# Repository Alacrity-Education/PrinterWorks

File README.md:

# PrinterWorks

Our 3D printer mods and PCB's

| [CANDU](CANDU) | [INDXWorx](INDXWorx) | [KliFan](KliFan) |
| :--: | :--: | :--: |
|  |  |  |

| [PIPSU](PIPSU) | [PDU20V](PDU20V) |
| :--: | :--: |
|  |  |

## RBARF

| [V0.1](RBARF-V0.1) | [V0.2](RBARF-V0.2) | [V0.3](RBARF-V0.3) |
| :--: | :--: | :--: |
|  |  |  |

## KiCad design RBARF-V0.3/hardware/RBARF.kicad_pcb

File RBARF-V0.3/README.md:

# RBARF V0.3

The same board as [RBARF V0.2](../RBARF-V0.2) (STM32C011D6, TPS7A02 LDO), with
the Q1 MOSFET footprint fixed.

Programming and debug pads: `SWDIO`, `SWCLK` and `UART`.

|  |  |
| -- | -- |

## Firmware

Rust + Embassy, in `firmware/`. See [firmware/README.md](firmware/README.md).

```sh
cd firmware
cargo build --release
cargo run --release    # flash with probe-rs
```

The C parity test (`cargo test-anim`) compiles the V0.1 animation engine from
`RBARF-V0.1/firmware/app/`.

The same firmware runs on [V0.2](../RBARF-V0.2).

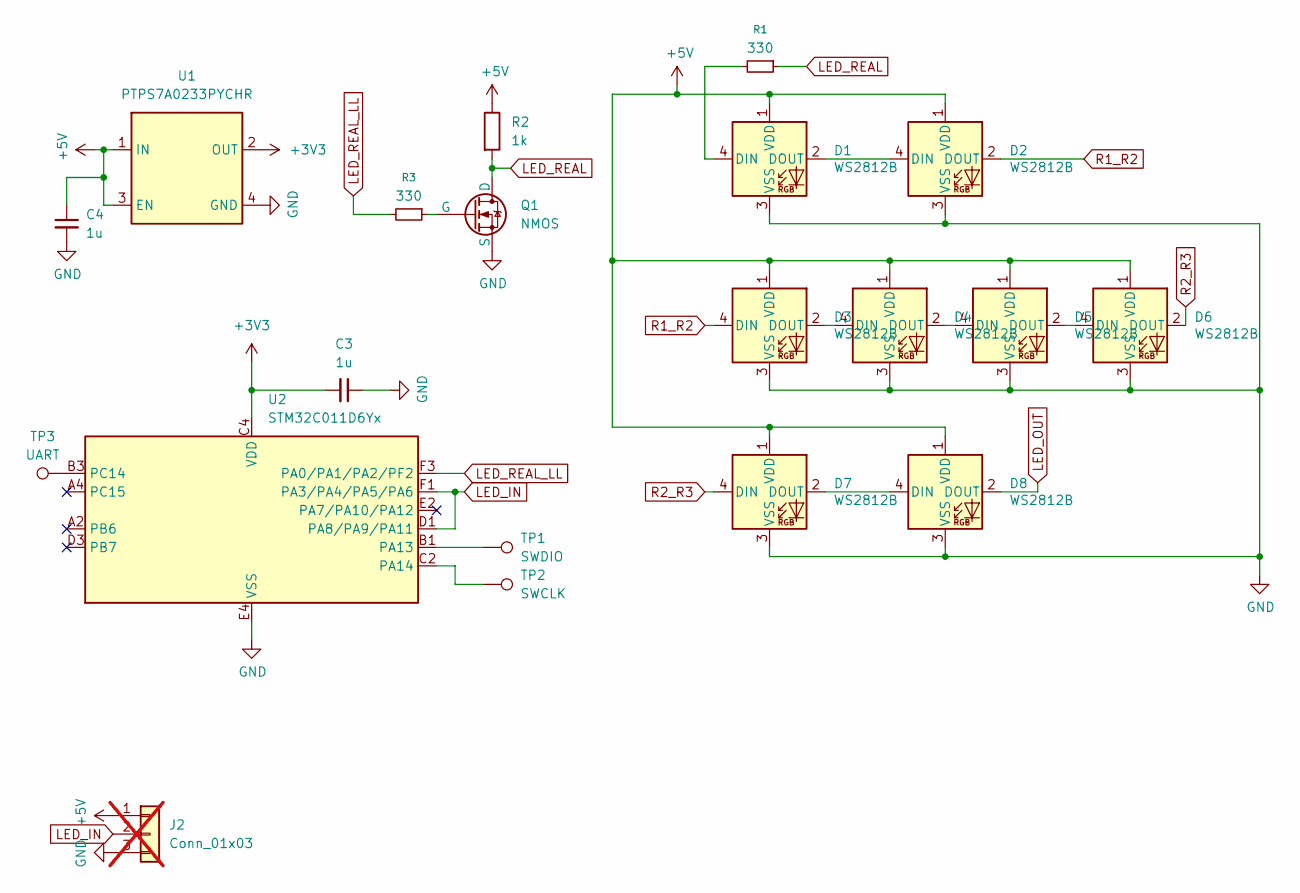
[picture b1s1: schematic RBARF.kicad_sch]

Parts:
C3, C4: 1u; C_0603_1608Metric; LCSC C29936
D1, D2, D3, D4, D5, D6, D7, D8: WS2812B; WS2812B-2020
J2: Conn_01x03; PinHeader_1x03_P1.00mm_Vertical_SMD_Pin1Left; not fitted
Q1: NMOS; TRXDFN100X60X40-3N
R1, R3: 330; R_0402_1005Metric; LCSC C105875
R2: 1k; R_0402_1005Metric
TP1: SWDIO; TestPoint_Pad_D1.0mm
TP2: SWCLK; TestPoint_Pad_D1.0mm
TP3: UART; TestPoint_Pad_D1.0mm
U1: PTPS7A0233PYCHR; YCH0004A-MFG
U2: STM32C011D6Yx; ST_WLCSP-12_1.7x1.42mm_Layout4x6_P0.35mm_Stagger

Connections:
+3V3: C3.2, U1.2 (OUT), U2.C4 (VDD)
+5V: C4.1, D1.1 (VDD), D2.1 (VDD), D3.1 (VDD), D4.1 (VDD), D5.1 (VDD), D6.1 (VDD), D7.1 (VDD), D8.1 (VDD), J2.1, R2.1, U1.1 (IN), U1.3 (EN)
GND: C3.1, C4.2, D1.3 (VSS), D2.3 (VSS), D3.3 (VSS), D4.3 (VSS), D5.3 (VSS), D6.3 (VSS), D7.3 (VSS), D8.3 (VSS), J2.3, Q1.3 (S), U1.4 (GND), U2.E4 (VSS)
LED_IN: J2.2, U2.D1 (PA8/PA9/PA11), U2.F1 (PA3/PA4/PA5/PA6)
LED_OUT: D8.2 (DOUT)
LED_REAL: Q1.1 (D), R1.1, R2.2
LED_REAL_LL: R3.2, U2.F3 (PA0/PA1/PA2/PF2)
unnamed: D1.4 (DIN), R1.2
unnamed: D1.2 (DOUT), D2.4 (DIN)
unnamed: D3.2 (DOUT), D4.4 (DIN)
unnamed: D4.2 (DOUT), D5.4 (DIN)
unnamed: D5.2 (DOUT), D6.4 (DIN)
unnamed: D7.2 (DOUT), D8.4 (DIN)
unnamed: Q1.2 (G), R3.1
unnamed: TP1.1 (1_1), U2.B1 (PA13)
unnamed: TP2.1 (1_1), U2.C2 (PA14)
unnamed: TP3.1 (1_1), U2.B3 (PC14)
R1_R2: D2.2 (DOUT), D3.4 (DIN)
R2_R3: D6.2 (DOUT), D7.4 (DIN)

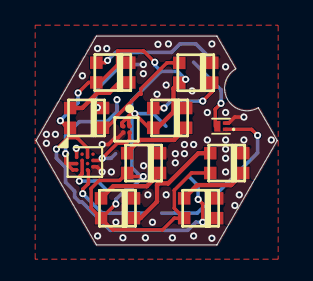
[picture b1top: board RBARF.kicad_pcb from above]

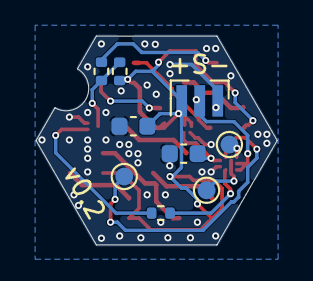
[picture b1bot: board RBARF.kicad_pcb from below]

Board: 2 copper layers, 13.4 x 11.6 mm, 20 parts (9 on the bottom side), 18 nets.

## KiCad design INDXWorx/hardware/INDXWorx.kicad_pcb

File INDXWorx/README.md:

# INDXWorx V0.1

An adapter that connects the Bondtech INDX Prusa head to a Klipper printer. It
is designed to plug into the BTT Octopus mainboard.

The head talks RS485. The board carries an ST STR485, a very high quality
RS485 transceiver, and gives the head switchable 5V power.

|  |  |
| -- | -- |

## Features

- **RS485** through the ST STR485 transceiver, with 120 Ω termination on the
  board.
- **Very good ESD protection and common-mode rejection** on the RS485 line: a
  common-mode choke (Murata DLW43SH), an ESD protection diode (NUP2105L) and
  100 pF C0G filter capacitors.
- **Clean supplies:** a TI TPS60151 flying-capacitor charge pump makes a clean
  5V from the Octopus 3.3V, and an MCP1825 LDO makes the board's own 3.3V.
- **Switchable 5V head power**, through a P-MOSFET.
- **LEDs** for board power, 5V head power and RS485 activity.
- **RS485 line swapper:** a DIP switch poka-yoke, so the two RS485 lines can be
  swapped without re-crimping the cable.

## Connections

### Octopus

The board plugs into the Octopus WiFi socket. It uses these Octopus pins:

| Octopus pin | Function |
| -- | -- |
| PD5 (TX3) | RS485 transmit |
| PD6 (RX3) | RS485 receive |
| PD7 | RS485 driver enable (DE) |
| PD10 | RS485 receiver enable (/RE, active low) |
| PG7 | Head 5V switch: on by default, drive high to switch the head off |

### Head

## RS485 line swapper

The silkscreen next to the DIP switch shows the two settings:

- **Straight (`| |`):** the two switches next to `| |` ON, the two next to
  `X` OFF.
- **Swapped (`X`):** the two switches next to `X` ON, the two next to `| |`
  OFF. The head's two RS485 lines are crossed.

Go by the silkscreen marks, not the numbers on the switch: the switch can be
fitted either way round.

Use one pair at a time: turning on all four switches shorts the RS485 lines.

## LEDs

The silkscreen `T/H/P` names the three LEDs:

- **T** (blue): traffic, RS485 activity.
- **H** (red): head power, the switched 5V to the head is on.
- **P** (orange): board power.

## Options

- `JP4` (`SLR`, on the back) is a solder jumper, open by default. Closing it
  ties the STR485 slew-rate pin to 3.3V; see the STR485 datasheet.

## Gallery

|  |  |
| -- | -- |
|  |  |
|  |  |

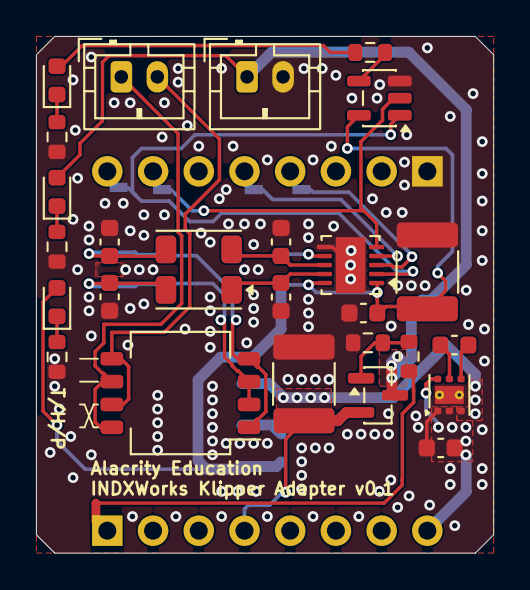
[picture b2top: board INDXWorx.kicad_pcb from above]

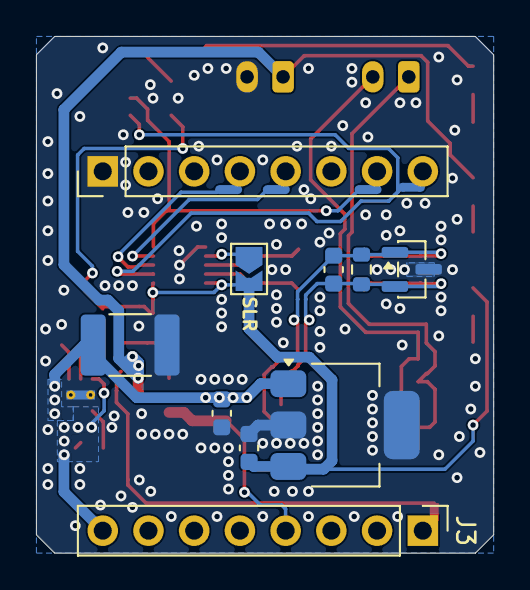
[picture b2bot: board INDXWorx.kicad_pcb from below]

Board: 2 copper layers, 25.4 x 28.7 mm, 41 parts (14 on the bottom side), 30 nets.

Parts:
C7, C8, C9, C10, C11: 100p; C_0603_1608Metric
C13, C14, C19: 10u; C_1812_4532Metric
C15: 100n; C_0603_1608Metric
C16, C17: 1u; C_0603_1608Metric
C18: 2.2u; C_0603_1608Metric
C20: 10u; C_0603_1608Metric
D2: NUP2105L; SOT-23
D3: PWR-ORANGE; LED_0603_1608Metric
D4: HEAD-RED; LED_0603_1608Metric
D5: PWR-BLUE; LED_0603_1608Metric
J3: WIFISOCKET_P1; PinHeader_1x08_P2.54mm_Vertical
J4: WIFISOCKET_P2; PinHeader_1x08_P2.54mm_Vertical
J8: RS485; JST_PH_B2B-PH-K_1x02_P2.00mm_Vertical
J9: 5V_SW; JST_PH_B2B-PH-K_1x02_P2.00mm_Vertical
JP4: SLR; SolderJumper-2_P1.3mm_Open_TrianglePad1.0x1.5mm
L2: muRata DLW43SH510XK2L; L_CommonModeChoke_Coilank_ACM4532
NT1, NT2, NT3, NT4, NT5: NetTie_2; NetTie-2_SMD_Pad0.5mm
Q1: AO3401A; SOT-23
R6, R8, R11, R12: 120; R_0603_1608Metric
R7: 10K; R_0603_1608Metric
R9, R10: 470; R_0603_1608Metric
SW3: LINE_SWAPPER; SW_DIP_SPSTx04_Slide_KingTek_DSHP04TS_W7.62mm_P1.27mm
U3: STR485; DFN-10-1EP_3x3mm_P0.5mm_EP1.646x3.1mm
U4: MCP1825S-3302E; SOT-223-3_TabPin2
U5: TPS60151DRV; WSON-6-1EP_2x2mm_P0.65mm_EP1x1.6mm_ThermalVias
U7: 74AHC1G02; SOT-23-5

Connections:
3V3_RAW: C20.1, J3.8, U5.2 (VIN), U5.6 (ENA)
5V_SW_GPIO: NT1.1, R8.1
+3.3V: C14.1, C15.1, C16.1, D3.2 (A), JP4.2 (B), U3.1 (VL), U3.10 (VCC), U4.3 (VO), U7.5 (VCC)
+5V: C13.1, C17.1, C19.1, J3.4, Q1.2 (S), U4.1 (VI), U5.3 (VOUT)
/5V_SW: D4.2 (A), J9.1, Q1.3 (D)
/RS485_CHIP+: C10.1, C11.1, D2.1 (K), L2.3, R6.1, SW3.1, SW3.4
/RS485_CHIP-: C9.1, C11.2, D2.2 (K), L2.2, R6.2, SW3.2, SW3.3
/RS485_HEAD+: J8.1, SW3.6, SW3.8
/RS485_HEAD-: J8.2, SW3.5, SW3.7
GND: C7.2, C8.2, C9.2, C10.2, C13.2, C14.2, C15.2, C16.2, C17.2, C19.2, C20.2, D2.3 (A), J4.1, J9.2, R7.1, R9.2, R10.2, R11.2, U3.6 (GND), U3.11 (GND), U4.2 (GND), U5.1 (GND), U5.7 (EP), U7.3 (GND)
MB_PD5/TX3: J4.7, NT5.2
MB_PD6/RX3: J4.8, NT2.2
MB_PD7: J4.4, NT4.2
MB_PD10: J4.5, NT3.2
MB_PG7: J3.1, NT1.2
unnamed: D3.1 (K), R10.1
unnamed: D4.1 (K), R9.1
unnamed: D5.2 (A), R12.1
unnamed: D5.1 (K), R11.1
unnamed: JP4.1 (A), U3.7 (SLR)
unnamed: Q1.1 (G), R7.2, R8.2
unnamed: R12.2, U7.4
unnamed: C7.1, L2.4, U3.8 (A)
unnamed: C8.1, L2.1, U3.9 (B)
unnamed: C18.1, U5.4 (CP+)
unnamed: C18.2, U5.5 (CP-)
RS485_DE: NT4.1, U3.3 (DE)
RS485_RX: NT2.1, U3.2 (R), U7.1
RS485_TX: NT5.1, U3.5 (D), U7.2
~RS485_RE: NT3.1, U3.4 (~RE)

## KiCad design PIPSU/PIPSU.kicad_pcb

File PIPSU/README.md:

# PIPSU

A tiny PSU for Raspberry Pi boards. It plugs straight into the Pi's USB-C
port and supplies 5V, up to 3A, from the printer's 24V supply line (it accepts
8-30V). We built it to take the Raspberry Pi's power draw off the mainboard's
regulator and use a more stable supply instead.

|  |  |  |
| -- | -- | -- |

The board uses TI's TPSM63603, an ultra-integrated power module, to keep the
footprint very small. Its high efficiency keeps the temperature manageable at
full load, on a very small board with completely passive cooling.

## Connections

All the pads are on the back of the board:

- **24V** and **GND** (large pads): the input from the printer's 24V supply
  (8-30V).
- **5V** and **GND** (small pads): 5V out, for powering peripherals.
- **DP** and **DN**: the USB 2.0 data lines of the USB-C plug, for connecting
  a USB device to the Pi.

The USB-C plug advertises a 3A source to the Pi on its CC line.

|  |  |
| -- | -- |

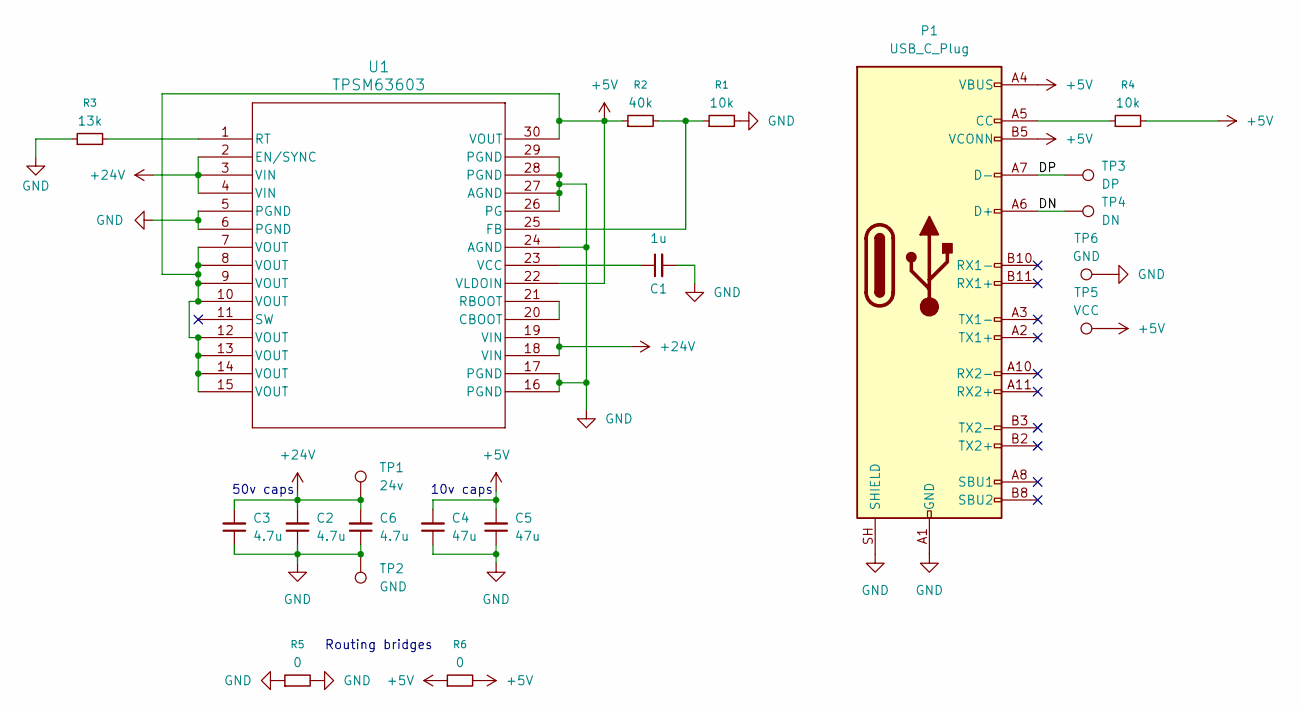
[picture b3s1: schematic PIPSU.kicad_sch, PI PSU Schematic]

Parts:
C1: 1u; C_0603_1608Metric; LCSC C29936
C2, C3, C6: 4.7u; C_1206_3216Metric; LCSC C51205
C4, C5: 47u; C_1210_3225Metric; LCSC C84494
P1: USB_C_Plug; USB_C_Plug_Molex_105444
R1, R4: 10k; R_0402_1005Metric; LCSC C2906861
R2: 40k; R_0402_1005Metric; LCSC C49654409
R3: 13k; R_0402_1005Metric; LCSC C2909319
R5, R6: 0; R_0805_2012Metric; LCSC C2907215
TP1: 24v; TestPoint_Pad_3.0x3.0mm
TP2: GND; TestPoint_Pad_3.0x3.0mm
TP3: DP; TestPoint_Pad_D1.0mm
TP4: DN; TestPoint_Pad_D1.0mm
TP5: VCC; TestPoint_Pad_D1.0mm
TP6: GND; TestPoint_Pad_D1.0mm
U1: TPSM63603; B0QFN30; LCSC C5219327

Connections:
+5V: C4.2, C5.2, P1.A4 (VBUS), P1.A9 (VBUS), P1.B4 (VBUS), P1.B5 (VCONN), P1.B9 (VBUS), R2.1, R4.2, R6.1, R6.2, TP5.1 (1_1), U1.7 (VOUT), U1.8 (VOUT), U1.9 (VOUT), U1.10 (VOUT), U1.12 (VOUT), U1.13 (VOUT), U1.14 (VOUT), U1.15 (VOUT), U1.22 (VLDOIN), U1.30 (VOUT)
+24V: C2.2, C3.2, C6.2, TP1.1 (1_1), U1.2 (EN/SYNC), U1.3 (VIN), U1.4 (VIN), U1.18 (VIN), U1.19 (VIN)
/DN: P1.A6 (D+), TP4.1 (1_1)
/DP: P1.A7 (D-), TP3.1 (1_1)
GND: C1.2, C2.1, C3.1, C4.1, C5.1, C6.1, P1.A1 (GND), P1.A12 (GND), P1.B1 (GND), P1.B12 (GND), P1.SH (SHIELD), R1.2, R3.1, R5.1, R5.2, TP2.1 (1_1), TP6.1 (1_1), U1.5 (PGND), U1.6 (PGND), U1.16 (PGND), U1.17 (PGND), U1.24 (AGND), U1.26 (PG), U1.27 (AGND), U1.28 (PGND), U1.29 (PGND)
unnamed: P1.A5 (CC), R4.1
unnamed: U1.20 (CBOOT), U1.21 (RBOOT)
unnamed: R1.1, R2.2, U1.25 (FB)
unnamed: R3.2, U1.1 (RT)
unnamed: C1.1, U1.23 (VCC)

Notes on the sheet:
Routing bridges
10v caps
50v caps

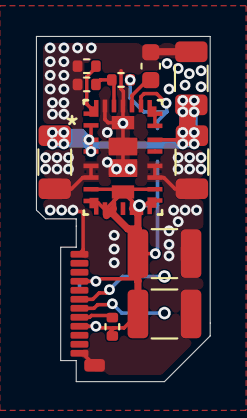
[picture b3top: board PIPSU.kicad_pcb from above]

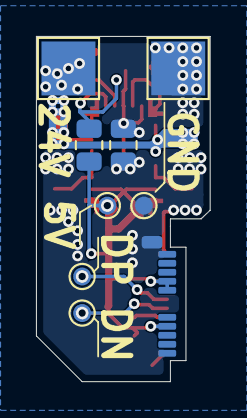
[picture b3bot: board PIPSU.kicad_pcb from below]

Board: 2 copper layers, 9.7 x 19.2 mm, 20 parts (8 on the bottom side), 10 nets.

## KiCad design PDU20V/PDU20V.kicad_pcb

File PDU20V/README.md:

# PDU20V

A rack power distribution board. It takes 20V from one big supply and shares
it out to the mini PCs and other devices in the rack, over XT90 connectors.

|  |  |
| -- | -- |

## Connectors

- **PSU side (J6, back of the board)**: one female AMASS XT90, for the lead
  from the 20V supply.
- **Outputs (J1-J5, J7-J10, front)**: nine male AMASS XT90s, one per mini PC
  or device.
- **Solder pads (TP1-TP4, back)**: two `+20V` and two `GND` 4×4mm pads, for
  wiring the supply or measuring.

All connectors are in parallel: every output gets the full 20V rail. There is
no fuse or switch on the board.

|  |
| -- |
|  |

## Mounting

The ten M3 holes are not isolated: the five along one long edge are on `+20V`
and the five along the other are on `GND`. Mount the board with nylon
standoffs or screws, or it will short the supply against a metal rack.

## Mini PCs

We use it with Dell OptiPlex 3060 Micro PCs. Fed from a shared supply instead
of the Dell charger, their BIOS throttles the CPU to 800 MHz.
[Dell3060ForcePower](https://github.com/Alacrity-Education/Dell3060ForcePower)
restores full clocks and turbo at every boot.

We use this board in our rack to save space and power: all the mini PCs run
from a single supply instead of one power brick each.

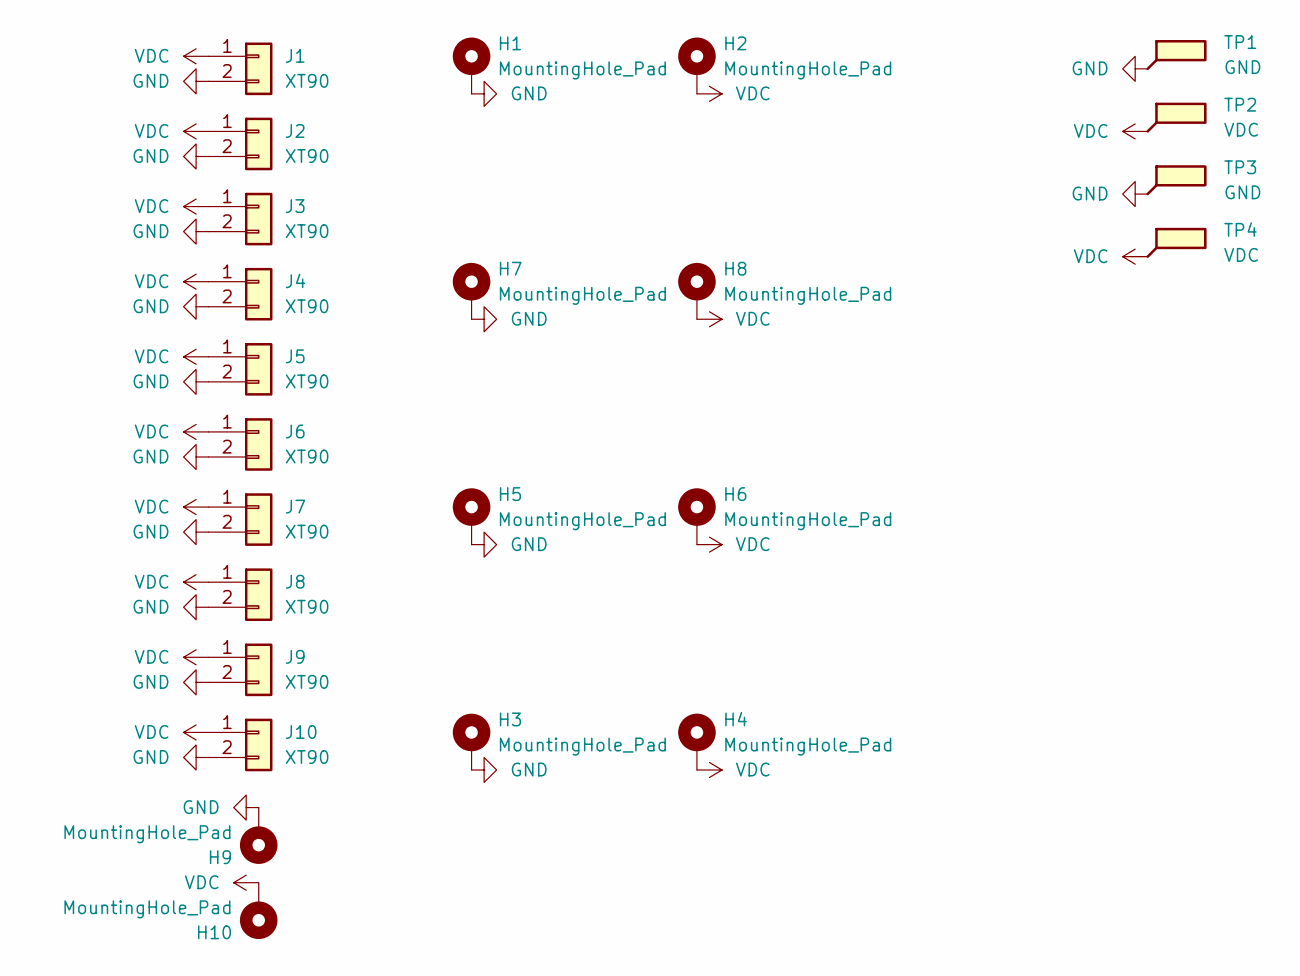
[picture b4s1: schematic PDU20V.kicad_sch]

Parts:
H1, H2, H3, H4, H5, H6, H7, H8, H9, H10: MountingHole_Pad; MountingHole_3.2mm_M3_Pad_Via
J1, J2, J3, J4, J5, J6, J7, J8, J9, J10: XT90; XT90 AMASS
TP1, TP3: GND; TestPoint_Pad_4.0x4.0mm
TP2, TP4: VDC; TestPoint_Pad_4.0x4.0mm

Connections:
GND: H1.1 (1_1), H3.1 (1_1), H5.1 (1_1), H7.1 (1_1), H9.1 (1_1), J1.2, J2.2, J3.2, J4.2, J5.2, J6.2, J7.2, J8.2, J9.2, J10.2, TP1.1 (1_1), TP3.1 (1_1)
VDC: H2.1 (1_1), H4.1 (1_1), H6.1 (1_1), H8.1 (1_1), H10.1 (1_1), J1.1, J2.1, J3.1, J4.1, J5.1, J6.1, J7.1, J8.1, J9.1, J10.1, TP2.1 (1_1), TP4.1 (1_1)

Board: 2 copper layers, 24 parts (5 on the bottom side), 2 nets, no tracks yet.

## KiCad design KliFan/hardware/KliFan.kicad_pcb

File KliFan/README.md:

# KliFan V1

A fan hub for Klipper printers. One PWM signal from the motherboard drives four
4-pin PWM fans, and a tiny microcontroller (STM8S001J3) reads the four tach
lines so the printer can watch the fans through a single endstop input. The
board takes 12V through one of its three 2-pin headers; the other two take
always-on 12V fans.

|  |  |
| -- | -- |

## Pinout

### J11: printer connection (JST-XH, 4-pin)

The vertical connector at the end of the board. It goes to the motherboard:
pins 1-3 to an endstop port, pin 4 to a free digital output.

```
              +-------+
  +5V    1 ---| [■]   |      <-- endstop port, 5V
  GND    2 ---| (o)   |]     <-- endstop port, GND
  TACH   3 ---| (o)   |]     --> endstop port, signal  (tach_out)
  PWM    4 ---| (o)   |      <-- motherboard digital output pin (fan PWM)
              +-------+
                       ^
                       tab
```

### Fan headers

The four 4-pin headers are PC-fan compatible: any standard 4-pin PWM PC fan
plugs straight in. Their speed follows the PWM signal on J11 pin 4, and the
microcontroller reads each fan's tach line.

The three 2-pin headers are standard 3D-printer 12V fan headers, all wired
in parallel. One of them must be connected to an always-on 12V fan header on
the motherboard, or directly to the 12V supply: this powers the whole board,
including the 4-pin fans. J9 is marked `SUPPLY` for this, but any of the three
works. The other two take always-on fans, which run at full speed whenever
the board has 12V.

The mounting holes H1 and H2 are connected to GND.

### Programming and options

- `TP1` (`SWIM`) is the programming pad. It shares the STM8 pin with TACH4.
- `JP1` is a solder jumper, open by default. Closing it connects TACH1 straight
  to J11 pin 3, so the board can be used without the microcontroller.

## Firmware

Not written yet.

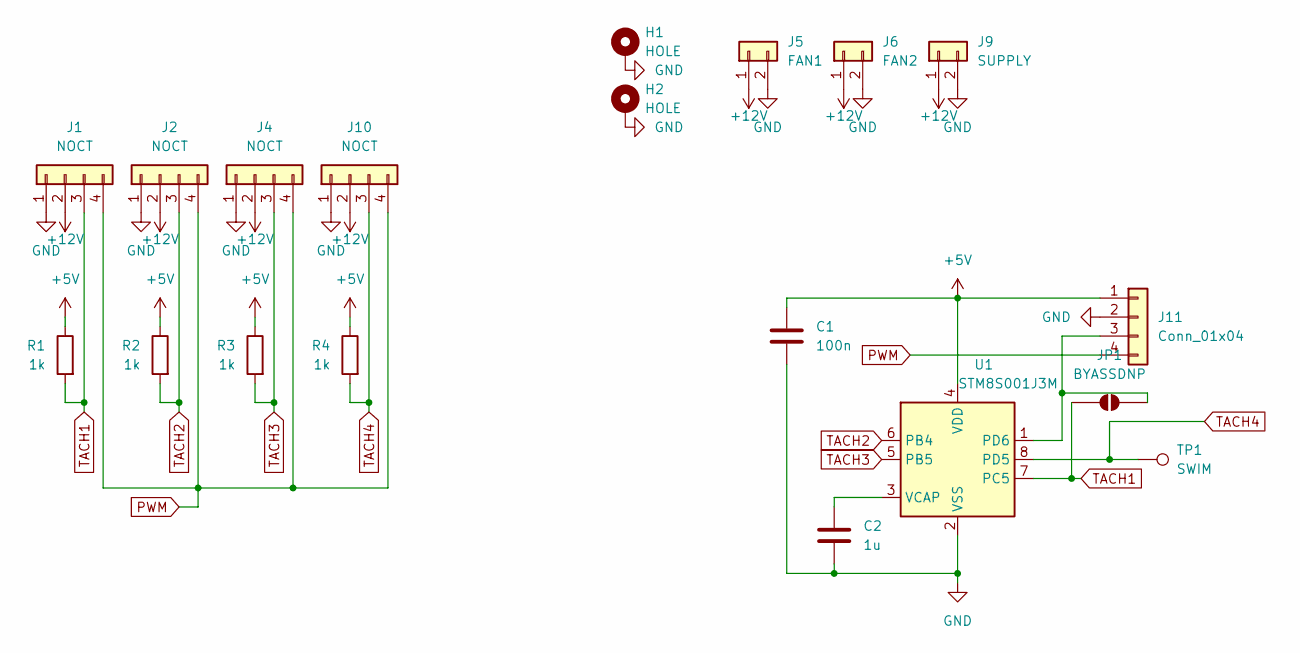
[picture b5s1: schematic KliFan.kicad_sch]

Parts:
C1: 100n; C_0603_1608Metric; LCSC C1591
C2: 1u; C_0603_1608Metric; LCSC C29936
H1, H2: HOLE; MountingHole_3.2mm_M3_Pad_Via
J1, J2, J4, J10: NOCT; FanPinHeader_1x04_P2.54mm_Vertical; LCSC C240840
J5: FAN1; JST_XH_B2B-XH-A_1x02_P2.50mm_Vertical; LCSC C158012
J6: FAN2; JST_XH_B2B-XH-A_1x02_P2.50mm_Vertical; LCSC C158012
J9: SUPPLY; JST_XH_B2B-XH-A_1x02_P2.50mm_Vertical; LCSC C158012
J11: Conn_01x04; JST_XH_B4B-XH-A_1x04_P2.50mm_Vertical; LCSC C566013
JP1: BYASSDNP; SolderJumper-2_P1.3mm_Open_TrianglePad1.0x1.5mm
R1, R2, R3, R4: 1k; R_0603_1608Metric; LCSC C2907002
TP1: SWIM; TestPoint_Pad_D1.5mm
U1: STM8S001J3M; SO-8_3.9x4.9mm_P1.27mm

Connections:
+5V: C1.1, J11.1, R1.1, R2.1, R3.1, R4.1, U1.4 (VDD)
+12V: J1.2, J2.2, J4.2, J5.1, J6.1, J9.1, J10.2
GND: C1.2, C2.2, H1.1 (1_1), H2.1 (1_1), J1.1, J2.1, J4.1, J5.2, J6.2, J9.2, J10.1, J11.2, U1.2 (VSS)
unnamed: J11.3, JP1.2 (B), U1.1 (PD6)
unnamed: C2.1, U1.3 (VCAP)
PWM: J1.4, J2.4, J4.4, J10.4, J11.4
TACH1: J1.3, JP1.1 (A), R1.2, U1.7 (PC5)
TACH2: J2.3, R2.2, U1.6 (PB4)
TACH3: J4.3, R3.2, U1.5 (PB5)
TACH4: J10.3, R4.2, TP1.1 (1_1), U1.8 (PD5)

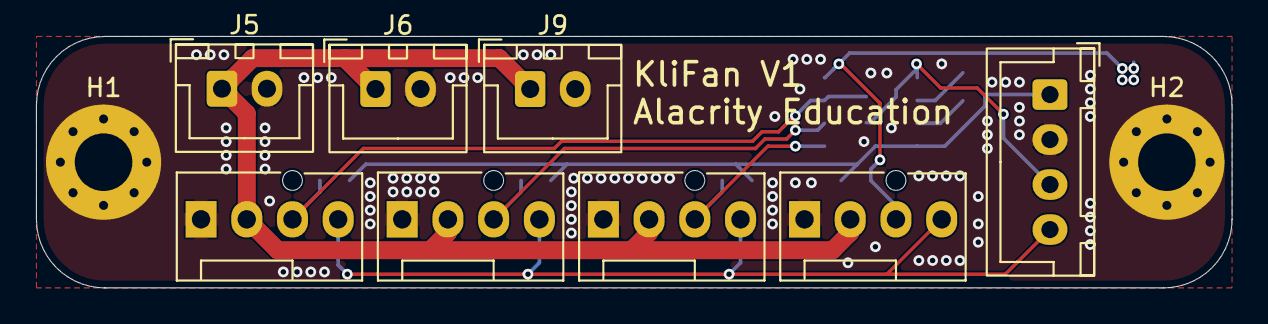
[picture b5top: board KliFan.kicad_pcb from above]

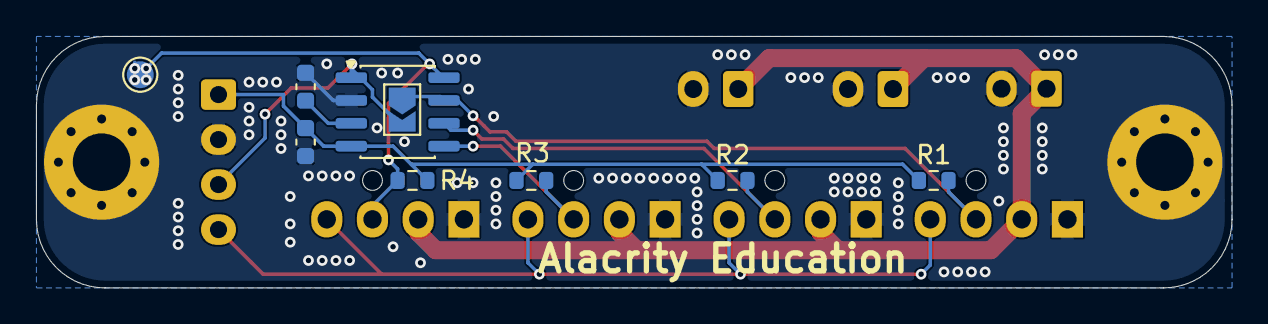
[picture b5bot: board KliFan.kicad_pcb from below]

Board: 2 copper layers, 66.4 x 14.0 mm, 19 parts (9 on the bottom side), 10 nets.

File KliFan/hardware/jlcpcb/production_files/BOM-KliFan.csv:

Comment,Designator,Footprint,LCSC,Quantity
100n,C1,C_0603_1608Metric,C1591,1
1k,"R1,R2,R3,R4",R_0603_1608Metric,C2907002,4
1u,C2,C_0603_1608Metric,C29936,1
Conn_01x04,J11,JST_XH_B4B-XH-A_1x04_P2.50mm_Vertical,C566013,1
FAN1,J5,JST_XH_B2B-XH-A_1x02_P2.50mm_Vertical,C378939,1
FAN2,J6,JST_XH_B2B-XH-A_1x02_P2.50mm_Vertical,C378939,1
NOCT,"J1,J10,J2,J4",FanPinHeader_1x04_P2.54mm_Vertical,C240840,4
SUPPLY,J9,JST_XH_B2B-XH-A_1x02_P2.50mm_Vertical,C378939,1
STM8S001J3M,U1,SO-8_3.9x4.9mm_P1.27mm,,1

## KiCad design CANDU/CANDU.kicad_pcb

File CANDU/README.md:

# CANDU V1.1

CAN DistribUtor is a board that distributes CAN and 24V power to multiple
toolheads or CAN devices, like ERCF MMUs.

The board has no active parts: every CAN connector is on the same bus, and
every power terminal is on the same 24V rail.

|  |  |  |
| -- | -- | -- |

## Ports

- 1x Power Uplink
- 1x CAN Uplink, by RJ45 connector
- 4x CAN+Power Downlinks to end devices
- 2x Extra CAN Downlinks
- 1x Power Downlink
- Power indicator LED: the LEDs in the RJ45 jack light up when the board has
  24V.

The board is self-documenting: crimping instructions and pinouts are printed
on the silkscreen.

## RJ45 pinout

4 pins of the RJ45 are mapped to CAN H, and the other 4 to CAN L.

## Swapping CAN H and L on the RJ45

The CAN L-H pair coming from the RJ45 jack can be swapped by rotating the
resistor placement near the jack by 90 degrees. R1 and R2 are two 0 Ω links
whose four pads form a square:

- **Straight (as built):** both links horizontal. RJ45 pins 5-8 go to CAN H,
  pins 1-4 to CAN L.
- **Swapped:** both links vertical, on the dashed outlines. RJ45 pins 1-4 go
  to CAN H, pins 5-8 to CAN L.

The swap only affects the RJ45 uplink.

## Notes

- The CAN bus needs a 120 Ω terminator at each end. The board has none, so terminate at the host and at the last device.
- If using long cables to the 2-4 devices, terminate at two devices instead of at the host. In this case, make sure the CANDU-Host cable is short.
- Four 330 µF high-quality capacitors (C1-C4) buffer the 24V rail.
- M3 mounting holes are connected to GND.

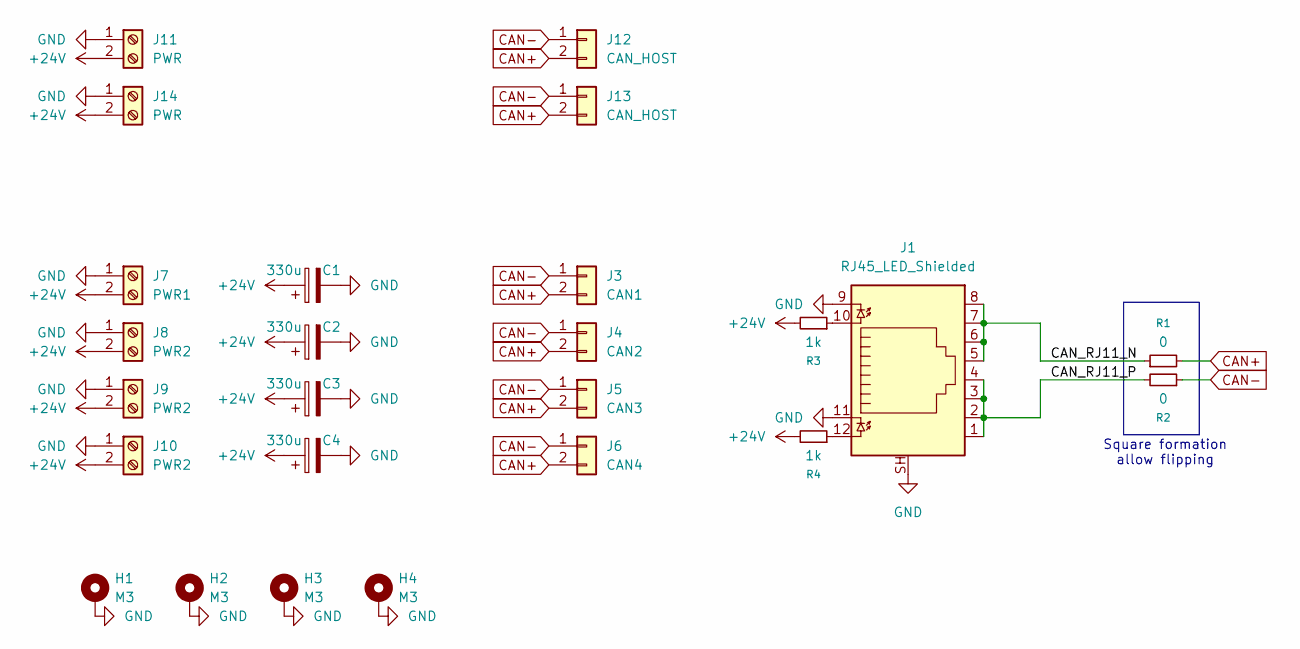
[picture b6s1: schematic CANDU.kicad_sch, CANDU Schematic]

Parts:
C1, C2, C3, C4: 330u; CP_Radial_D10.0mm_P5.00mm
H1, H2, H3, H4: M3; MountingHole_3.2mm_M3_Pad_Via
J1: RJ45_LED_Shielded; RJ45_Amphenol_RJHSE538X
J3: CAN1; JST_XH_B2B-XH-A_1x02_P2.50mm_Vertical; LCSC C158012
J4: CAN2; JST_XH_B2B-XH-A_1x02_P2.50mm_Vertical; LCSC C158012
J5: CAN3; JST_XH_B2B-XH-A_1x02_P2.50mm_Vertical; LCSC C158012
J6: CAN4; JST_XH_B2B-XH-A_1x02_P2.50mm_Vertical; LCSC C158012
J7: PWR1; Altech_AK300_1x02_P5.00mm_45-Degree
J8, J9, J10: PWR2; Altech_AK300_1x02_P5.00mm_45-Degree
J11, J14: PWR; Altech_AK300_1x02_P5.00mm_45-Degree
J12, J13: CAN_HOST; JST_XH_B2B-XH-A_1x02_P2.50mm_Vertical; LCSC C158012
R1, R2: 0; R_0805_2012Metric_Pad1.20x1.40mm_HandSolder; LCSC C2907215
R3, R4: 1k; R_0805_2012Metric_Pad1.20x1.40mm_HandSolder; LCSC C2907232

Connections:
+24V: C1.1, C2.1, C3.1, C4.1, J7.2, J8.2, J9.2, J10.2, J11.2, J14.2, R3.2, R4.2
/CAN_RJ11_N: J1.5, J1.6, J1.7, J1.8, R1.1
/CAN_RJ11_P: J1.1, J1.2, J1.3, J1.4, R2.2
CAN+: J3.2, J4.2, J5.2, J6.2, J12.2, J13.2, R1.2
CAN-: J3.1, J4.1, J5.1, J6.1, J12.1, J13.1, R2.1
GND: C1.2, C2.2, C3.2, C4.2, H1.1 (1_1), H2.1 (1_1), H3.1 (1_1), H4.1 (1_1), J1.9, J1.11, J1.SH, J7.1, J8.1, J9.1, J10.1, J11.1, J14.1
unnamed: J1.10, R3.1
unnamed: J1.12, R4.1

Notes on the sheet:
Square formation allow flipping

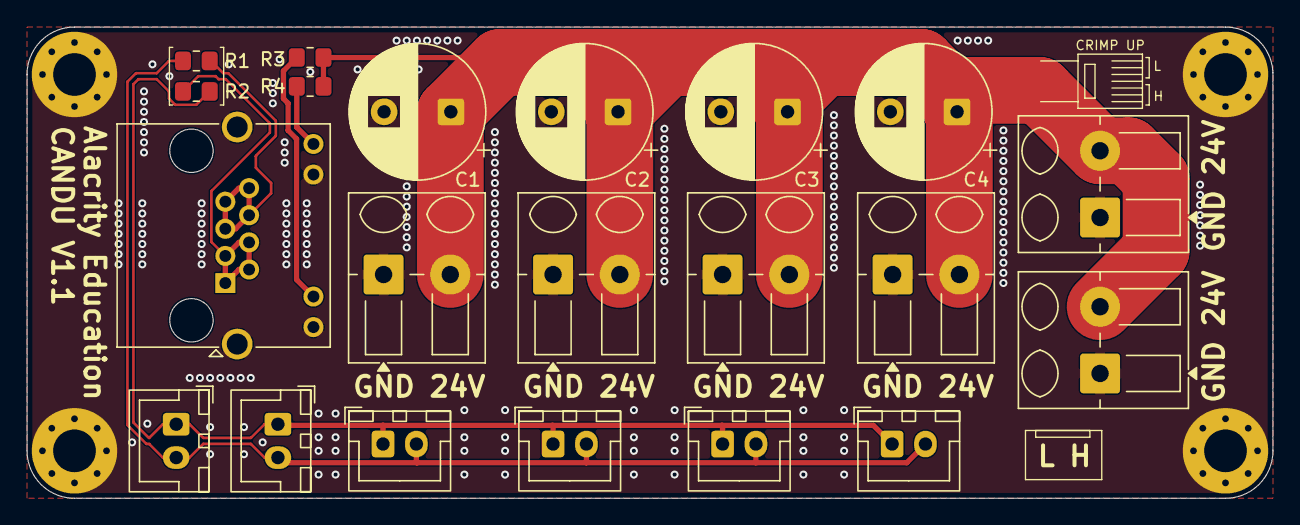
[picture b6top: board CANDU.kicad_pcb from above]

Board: 2 copper layers, 93.3 x 35.3 mm, 25 parts (0 on the bottom side), 8 nets.

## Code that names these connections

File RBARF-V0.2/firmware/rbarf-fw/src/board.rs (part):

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//!
//! | Ball | Use | Firmware |
//! |------|-----|----------|
//! | F3   | LED output (PF2-NRST / PA0 / PA1 / PA2, SYSCFG_CFGR3.PINMUX1) | **PA0 = TIM1_CH1 AF5**, PINMUX1 = 01; needs NRST_MODE = 10 (`optbytes.rs`) |
//! | B3   | TP3 UART | **PC14 = USART1_TX AF0**, 115200 8N1, TX only |
//! | B1   | TP1 SWDIO | PA13 — NEVER TOUCH |
//! | C2   | TP2 SWCLK | PA14 — NEVER TOUCH |
//! | F1   | LED_IN (PA3 / PA4 / PA5 / PA6, SYSCFG_CFGR3.PINMUX5) | **PA6 = TIM3_CH1 AF1 input**, no pull, PINMUX5 = 11 (receiver, feature `time-tim14`) |
//! | D1   | LED_IN (PA8 / PA11 [PA9], PINMUX2), shorted to F1 | PA8 and PA11 digital input, no pull (PINMUX2 left 00) |
//! | A2, A4, D3, E2 | unconnected | untouched |
//!
//! LED_IN — raw 5 V WS2812 input on balls D1 and F1 (PA3, PA4, PA5, PA6 and
//! PA8, PA9, PA11). HARD RULE: never configure any of them as output,
//! alternate-function OUTPUT, or with a pull-up/pull-down (5 V tolerance
//! needs pulls off; the balls are shorted, so one output fights the other
//! GPIOs on the net). The only exceptions, both set by [`rx_ball_select`]:
//! PA6 becomes AF1 = TIM3_CH1 with the channel configured as a capture INPUT
//! before the pin is muxed (a timer channel in input mode never drives its
//! pin), and PA8/PA11 go from analog to digital input as the design asks
//! for D1 (docs/INPUT_CAPTURE_OPTIONS.md §4.1; RM0490 may not apply PINMUX2
//! on WLCSP12, PINOUT.md "Discrepancy on D1"). PA3, PA4, PA5 and PA9 stay in
//! their reset (analog) state; SECURE_MUXING_EN forces the unselected F1
//! GPIOs to input anyway.
//!
//! Also never touch PA1, PA2, PF2 (the other GPIOs of ball F3): only PA0 is
//! selected by PINMUX1. Debug is SWD only with no NRST wire: there is no
//! connect-under-reset, so PA13/PA14 must stay SWD AF0 and the firmware must
//! never enter Stop/Standby.
//!
//! LED output stage: Q1 NMOS inverter. MCU HIGH = LED DIN LOW (idle/latch),
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
/// LED data pin (ball F3).
#[cfg(feature = "out-pwm")]
pub type LedPin = peripherals::PA0;
/// SYSCFG_CFGR3.PINMUX1 value selecting `LedPin` on ball F3.
#[cfg(feature = "out-pwm")]
const LED_PINMUX1: Pinmux1 = Pinmux1::PA0;
/// GPIOA pin number of `LedPin` (for the pre-drive below).
#[cfg(feature = "out-pwm")]
const LED_PIN_N: usize = 0;

/// Timer + channel driving `LedPin` (PA0 AF5 = TIM1_CH1).
#[cfg(feature = "out-pwm")]
pub type LedTimer = peripherals::TIM1;
/// Must match `LedPin`.
#[cfg(feature = "out-pwm")]
pub type LedTimerChannel = embassy_stm32::timer::Ch1;
/// Alternate function number of TIM1_CH1 on PA0 (DS13866 table 13).
#[cfg(feature = "out-pwm")]
const LED_PIN_AF: u8 = 5;

/// SPI backend (feature `out-spi`, off by default): PA2 = SPI1_MOSI AF0.
#[cfg(feature = "out-spi")]
pub type LedPin = peripherals::PA2;
#[cfg(feature = "out-spi")]
const LED_PINMUX1: Pinmux1 = Pinmux1::PA2;
#[cfg(feature = "out-spi")]
const LED_PIN_N: usize = 2;
#[cfg(feature = "out-spi")]
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// update interrupt marks the latch gap. Only with feature `time-tim14`
// (TIM3 is the time driver otherwise).

/// LED_IN GPIO on ball F1 (TIM3_CH1).
#[cfg(feature = "time-tim14")]
pub type RxPin = peripherals::PA6;
#[cfg(feature = "time-tim14")]
const RX_PIN_N: usize = 6;
/// AF1 = TIM3_CH1 on PA6 (DS13866 table 13).
#[cfg(feature = "time-tim14")]
const RX_PIN_AF: u8 = 1;
/// SYSCFG_CFGR3.PINMUX5 = 11 connects PA6 to ball F1.
#[cfg(feature = "time-tim14")]
const RX_PINMUX5: Pinmux5 = Pinmux5::PA6;
/// GPIOs on ball D1, kept as plain inputs.
#[cfg(feature = "time-tim14")]
const RX_D1_PINS: [usize; 2] = [8, 11];
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// ---- UART (TP3) --------------------------------------------------------------

pub type UartPeri = peripherals::USART1;
pub type UartTxPin = peripherals::PC14;
pub const UART_BAUD: u32 = 115_200;
/// UART TX DMA (usart1_tx). Uses the last DMA channel: a 4d diagnostic
/// receiver build (design doc §3.4) would have to take it back.
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}

impl Board {
    /// Moves the board's peripherals out of `p`. PA13/PA14, the LED_IN pins
    /// and the other F3 GPIOs are deliberately never taken.
    pub fn take(p: Peripherals) -> Self {
        Board {
            led: LedPeripherals {
                #[cfg(feature = "out-pwm")]
                pin: p.PA0,
                #[cfg(feature = "out-pwm")]
                tim: p.TIM1,
                #[cfg(feature = "out-spi")]
                pin: p.PA2,
                #[cfg(feature = "out-spi")]
                spi: p.SPI1,
                dma: p.DMA1_CH1,
            },
            uart: p.USART1,
            uart_tx: p.PC14,
            uart_dma: p.DMA1_CH3,
            #[cfg(feature = "time-tim14")]
            time_tim: p.TIM14,
            #[cfg(feature = "time-tim14")]
            rx: RxPeripherals {
                pin: p.PA6,
                tim: p.TIM3,
                dma: p.DMA1_CH2,
            },
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        .modify(|w| w.set_moder(LED_PIN_N, pac::gpio::vals::Moder::ALTERNATE));
}

/// Connects LED_IN to the receiver: PA6 = AF1 (TIM3_CH1) input on ball F1,
/// and PA8/PA11 (ball D1) as digital inputs. No pull anywhere.
///
/// Call only after TIM3 CH1/CH2 are configured as capture inputs (CCxS != 00),
/// so the timer never drives the pin. Order: pull off, open-drain (defence
/// in depth: even a mis-configured channel could then never drive the 5 V
/// line high), AF number, MODER = alternate, and only then PINMUX5. Until
/// PINMUX5 selects PA6, SECURE_MUXING_EN keeps PA6 a disconnected input.
#[cfg(feature = "time-tim14")]
pub fn rx_ball_select() {
    use pac::gpio::vals::{Moder, Ot, Pupdr};
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    pac::SYSCFG.cfgr3().modify(|w| w.set_pinmux5(RX_PINMUX5));
}

/// LED_IN level as the GPIO sees it (IDR bit of `RxPin`), for diagnostics.
#[cfg(feature = "time-tim14")]
pub fn rx_pin_level() -> bool {
    pac::GPIOA.idr().read().idr(RX_PIN_N) == pac::gpio::vals::Idr::HIGH
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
